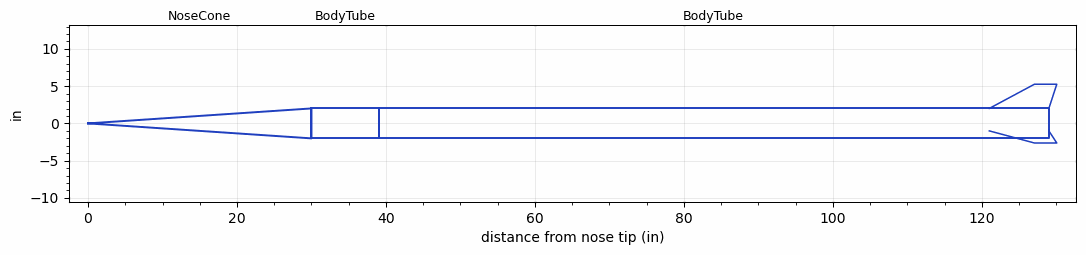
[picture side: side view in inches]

<RASAeroDocument>
 <FileVersion>2</FileVersion>
 <RocketDesign>
  <NoseCone>
   <Length>30</Length>
   <Diameter>4.02</Diameter>
   <Shape>Conical</Shape>
   <Location>0</Location>
  </NoseCone>
  <BodyTube>
   <Length>9</Length>
   <Diameter>4.02</Diameter>
   <Location>30</Location>
   <Protuberance>
    <StreamlinedNoBaseDrag>0</StreamlinedNoBaseDrag>
    <StreamlinedWithBaseDrag>0</StreamlinedWithBaseDrag>
    <InclinedPlate1Angle>90</InclinedPlate1Angle>
    <InclinedPlate1FrontalArea>3.5</InclinedPlate1FrontalArea>
    <InclinedPlate2Angle>90</InclinedPlate2Angle>
    <InclinedPlate2FrontalArea>3.5</InclinedPlate2FrontalArea>
   </Protuberance>
  </BodyTube>
  <BodyTube>
   <Length>90</Length>
   <Diameter>4.02</Diameter>
   <RailGuideDiameter>0.63</RailGuideDiameter>
   <RailGuideHeight>0.44</RailGuideHeight>
   <Location>39</Location>
   <Fin>
    <Count>3</Count>
    <Chord>8</Chord>
    <Span>3.25</Span>
    <SweepDistance>6.0622</SweepDistance>
    <TipChord>3</TipChord>
    <Thickness>0.1181</Thickness>
    <LERadius>0.04</LERadius>
    <Location>8</Location>
    <AirfoilSection>Hexagonal</AirfoilSection>
    <FX1>0.5</FX1>
    <FX3>0.25</FX3>
   </Fin>
  </BodyTube>
  <Surface>Smooth (Zero Roughness)</Surface>
  <ModifiedBarrowman>True</ModifiedBarrowman>
  <Turbulence>False</Turbulence>
  <UseBooster1>False</UseBooster1>
  <UseBooster2>False</UseBooster2>
 </RocketDesign>
 <LaunchSite>
  <Altitude>0</Altitude>
  <Pressure>0</Pressure>
  <RodAngle>3</RodAngle>
  <RodLength>17</RodLength>
  <Temperature>75</Temperature>
  <WindSpeed>8</WindSpeed>
 </LaunchSite>
 <Recovery>
  <Altitude1>1000</Altitude1>
  <Altitude2>1000</Altitude2>
  <DeviceType1>Parachute</DeviceType1>
  <DeviceType2>Parachute</DeviceType2>
  <Event1>True</Event1>
  <Event2>True</Event2>
  <Size1>72</Size1>
  <Size2>72</Size2>
  <EventType1>Apogee</EventType1>
  <EventType2>Altitude</EventType2>
  <CD1>0.24</CD1>
  <CD2>1.96</CD2>
 </Recovery>
 <SimulationList>
  <Simulation>
   <SustainerEngine>N5800-CS  (CTI)</SustainerEngine>
   <SustainerLaunchWt>67.3</SustainerLaunchWt>
   <SustainerNozzleDiameter>2.7</SustainerNozzleDiameter>
   <SustainerCG>82.8</SustainerCG>
   <SustainerIgnitionDelay>0</SustainerIgnitionDelay>
   <Booster1SeparationDelay>0</Booster1SeparationDelay>
   <Booster1IgnitionDelay>0</Booster1IgnitionDelay>
   <IncludeBooster1>False</IncludeBooster1>
   <Booster2Delay>0</Booster2Delay>
   <IncludeBooster2>False</IncludeBooster2>
   <TimetoApogee>42.77883</TimetoApogee>
   <MaxAltitude>35357.91</MaxAltitude>
   <MaxVelocity>2277.094</MaxVelocity>
  </Simulation>
  <Simulation>
   <SustainerEngine>M2500T  (AT)</SustainerEngine>
   <SustainerLaunchWt>52.4</SustainerLaunchWt>
   <SustainerNozzleDiameter>2.7</SustainerNozzleDiameter>
   <SustainerCG>79.85</SustainerCG>
   <SustainerIgnitionDelay>0</SustainerIgnitionDelay>
   <Booster1SeparationDelay>0</Booster1SeparationDelay>
   <Booster1IgnitionDelay>0</Booster1IgnitionDelay>
   <IncludeBooster1>False</IncludeBooster1>
   <Booster2Delay>0</Booster2Delay>
   <IncludeBooster2>False</IncludeBooster2>
   <TimetoApogee>30.93061</TimetoApogee>
   <MaxAltitude>16256.7</MaxAltitude>
   <MaxVelocity>1254.246</MaxVelocity>
  </Simulation>
 </SimulationList>
</RASAeroDocument>
